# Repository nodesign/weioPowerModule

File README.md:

WeIO-PowerModule
================

PowerModule for WeIO board

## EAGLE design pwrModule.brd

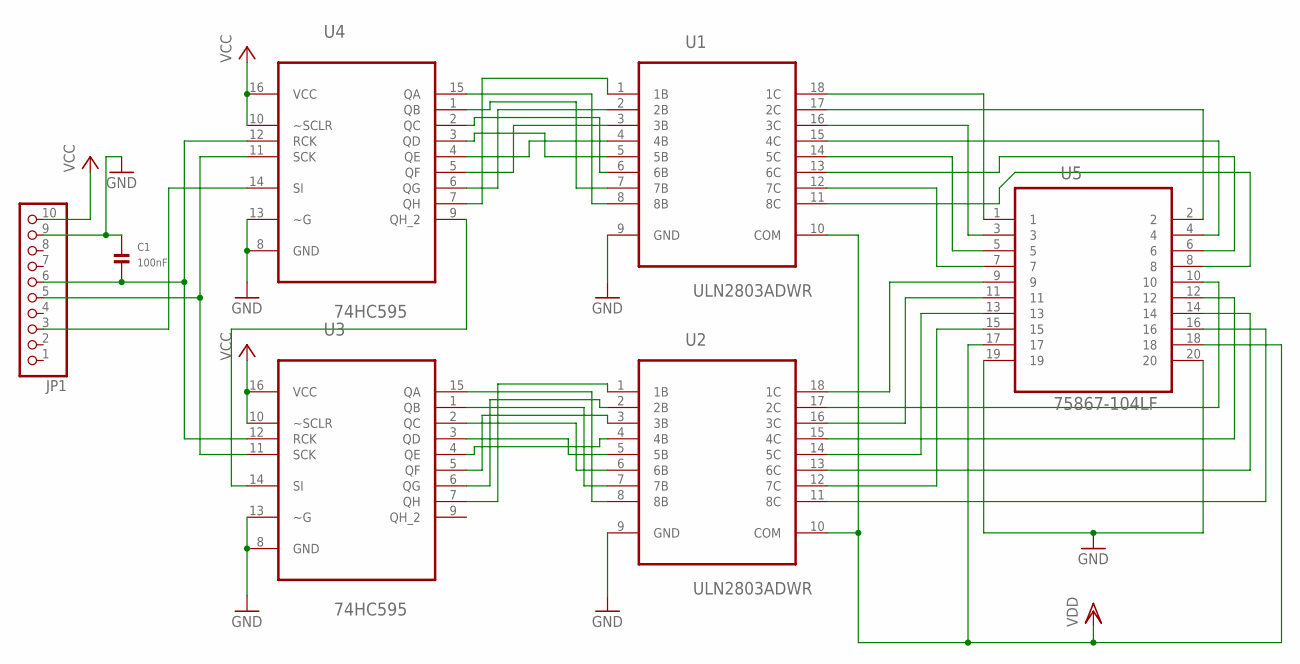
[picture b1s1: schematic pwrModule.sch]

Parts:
C1: 100nF; 0805
JP1: PINHD-1X10/90; 1X10/90
U1, U2: ULN2803ADWR; SOIC127P1030X265-18N
U3, U4: 74HC595; SOIC127P600X175-16N
U5: 75867-104LF; FCI_75867-104LF

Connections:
GND: C1.1, JP1.9, U1.9 (GND), U2.9 (GND), U3.8 (GND), U3.13 (~G), U4.8 (GND), U4.13 (~G), U5.19, U5.20
unnamed: C1.2, JP1.6, U3.12 (RCK), U4.12 (RCK)
unnamed: JP1.5, U3.11 (SCK), U4.11 (SCK)
unnamed: U3.14 (SI), U4.9 (QH_2)
unnamed: U1.18 (1C), U5.1
unnamed: U2.8 (8B), U3.15 (QA)
unnamed: U2.7 (7B), U3.1 (QB)
unnamed: U2.6 (6B), U3.2 (QC)
unnamed: U2.5 (5B), U3.3 (QD)
unnamed: U2.4 (4B), U3.4 (QE)
unnamed: U2.3 (3B), U3.5 (QF)
unnamed: U2.2 (2B), U3.6 (QG)
unnamed: U2.1 (1B), U3.7 (QH)
unnamed: U1.1 (1B), U4.7 (QH)
unnamed: U1.2 (2B), U4.6 (QG)
unnamed: U1.3 (3B), U4.5 (QF)
unnamed: U1.4 (4B), U4.4 (QE)
unnamed: U1.5 (5B), U4.3 (QD)
unnamed: U1.8 (8B), U4.15 (QA)
unnamed: U1.7 (7B), U4.1 (QB)
unnamed: U1.6 (6B), U4.2 (QC)
unnamed: JP1.3, U4.14 (SI)
unnamed: U1.17 (2C), U5.2
unnamed: U1.16 (3C), U5.3
unnamed: U1.15 (4C), U5.4
unnamed: U1.14 (5C), U5.5
unnamed: U1.13 (6C), U5.6
unnamed: U1.12 (7C), U5.7
unnamed: U1.11 (8C), U5.8
unnamed: U2.18 (1C), U5.9
unnamed: U2.17 (2C), U5.10
unnamed: U2.16 (3C), U5.11
unnamed: U2.15 (4C), U5.12
unnamed: U2.14 (5C), U5.13
unnamed: U2.13 (6C), U5.14
unnamed: U2.12 (7C), U5.15
unnamed: U2.11 (8C), U5.16
VCC: JP1.10, U3.10 (~SCLR), U3.16 (VCC), U4.10 (~SCLR), U4.16 (VCC)
VDD: U1.10 (COM), U2.10 (COM), U5.17, U5.18

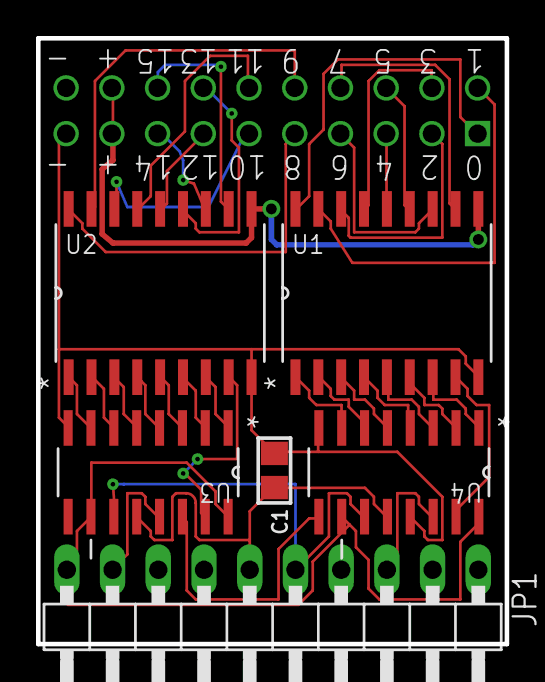
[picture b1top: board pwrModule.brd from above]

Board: 2 copper layers, 26.0 x 33.7 mm, 7 parts (1 on the bottom side), 39 nets.

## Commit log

2014-10-10 Power module schematics, board and part library

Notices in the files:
parts and their libraries:
microbuilder: This work is placed in the public domain, and may be freely used for commercial and non-commercial work with the following conditions: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
